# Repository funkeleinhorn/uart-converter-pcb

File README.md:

# My first PCB (an UART Converter)

This is the first PCB I have designed to learn [KiCad](https://www.kicad.org/).
It is an USB-C to UART Converter supporting 3.3V using an [FT230X](https://ftdichip.com/wp-content/uploads/2021/10/DS_FT230X.pdf).
Thanks a lot to [@Cutie-PHY](https://fosstodon.org/@sad_electronics) for teaching me KiCad and helping me to get this PCB designed and manufactured.

This project is licensed as open hardware. See LICENSE.txt for details.

## Images

Here you can see how the PCB looks:

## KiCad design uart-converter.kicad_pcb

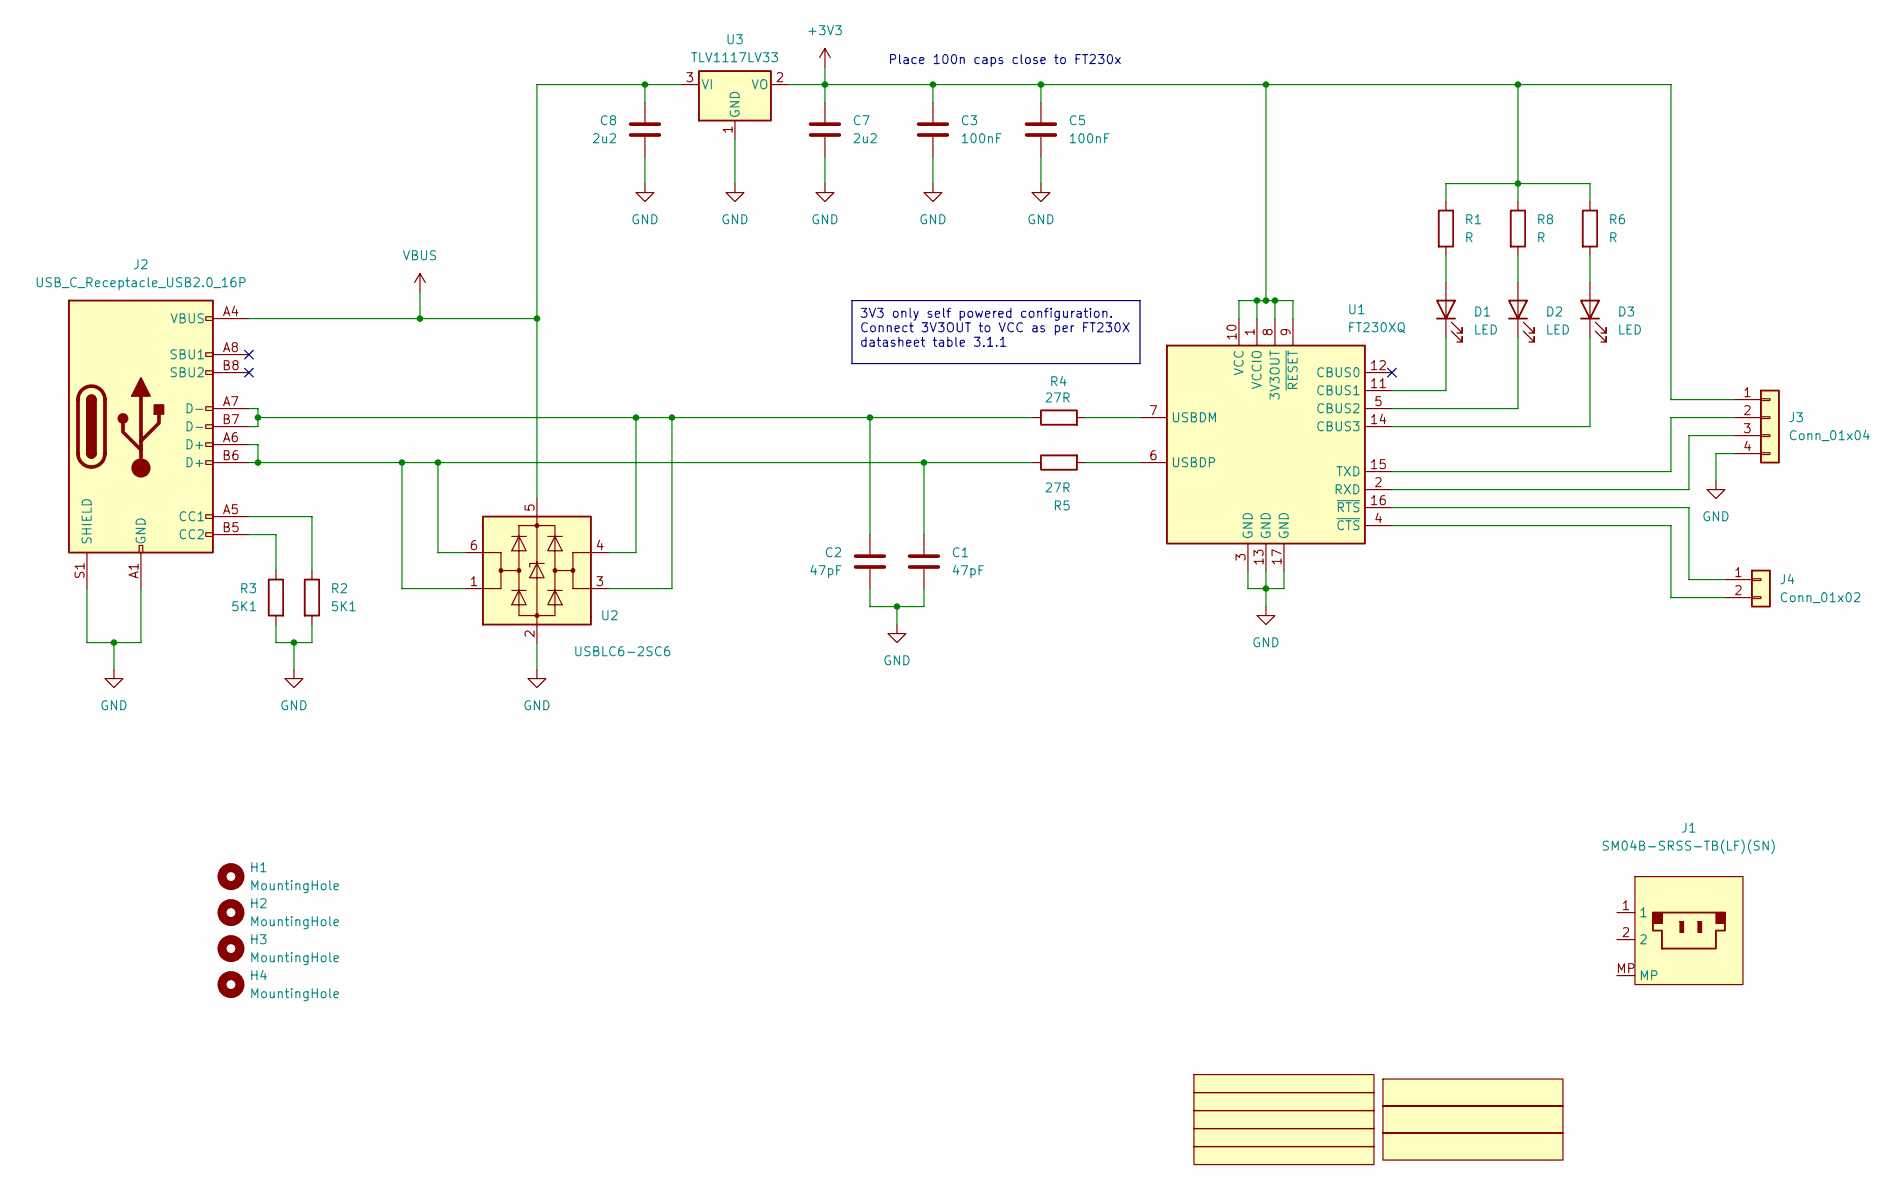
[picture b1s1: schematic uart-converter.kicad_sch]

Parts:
C1, C2: 47pF; C_0603_1608Metric
C3, C5: 100nF; C_0603_1608Metric
C7, C8: 2u2; C_0805_2012Metric
D1, D2, D3: LED; LED_0603_1608Metric
H1, H2, H3, H4: MountingHole; MountingHole_3.2mm_M3_DIN965
J1: SM04B-SRSS-TB(LF)(SN); MPN SM04B-SRSS-TB(LF)(SN)
J2: USB_C_Receptacle_USB2.0_16P; USB_C_Receptacle_JAE_DX07S016JA1R1500
J3: Conn_01x04; PinHeader_1x04_P2.54mm_Horizontal
J4: Conn_01x02; PinHeader_1x02_P2.54mm_Horizontal
R1, R6, R8: R; R_0603_1608Metric
R2, R3: 5K1; R_0603_1608Metric
R4, R5: 27R; R_0603_1608Metric
U1: FT230XQ; QFN-16-1EP_4x4mm_P0.65mm_EP2.1x2.1mm
U2: USBLC6-2SC6; SOT-23-6
U3: TLV1117LV33; SOT-223-3_TabPin2

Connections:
+3V3: C3.1, C5.1, C7.1, J3.1, R1.1, R6.1, R8.1, U1.1 (VCCIO), U1.8 (3V3OUT), U1.9 (~RESET), U1.10 (VCC), U3.2 (VO)
GND: C1.2, C2.2, C3.2, C5.2, C7.2, C8.2, J2.A1 (GND), J2.A12 (GND), J2.B1 (GND), J2.B12 (GND), J2.S1 (SHIELD), J3.4, R2.2, R3.2, U1.3 (GND), U1.13 (GND), U1.17 (GND), U2.2 (GND), U3.1 (GND)
unnamed: C1.1, J2.A6 (D+), J2.B6 (D+), R5.1, U2.1 (I/O1), U2.6 (I/O1)
unnamed: C2.1, J2.A7 (D-), J2.B7 (D-), R4.1, U2.3 (I/O2), U2.4 (I/O2)
unnamed: D1.2 (A), R1.2
unnamed: D1.1 (K), U1.11 (CBUS1)
unnamed: D2.2 (A), R8.2
unnamed: D2.1 (K), U1.5 (CBUS2)
unnamed: D3.2 (A), R6.2
unnamed: D3.1 (K), U1.14 (CBUS3)
unnamed: J2.A5 (CC1), R2.1
unnamed: J2.B5 (CC2), R3.1
unnamed: J3.2, U1.15 (TXD)
unnamed: J3.3, U1.2 (RXD)
unnamed: J4.1, U1.16 (~RTS)
unnamed: J4.2, U1.4 (~CTS)
unnamed: R4.2, U1.7 (USBDM)
unnamed: R5.2, U1.6 (USBDP)
VBUS: C8.1, J2.A4 (VBUS), J2.A9 (VBUS), J2.B4 (VBUS), J2.B9 (VBUS), U2.5 (VBUS), U3.3 (VI)

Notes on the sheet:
3V3 only self powered configuration. Connect 3V3OUT to VCC as per FT230X datasheet table 3.1.1
Place 100n caps close to FT230x

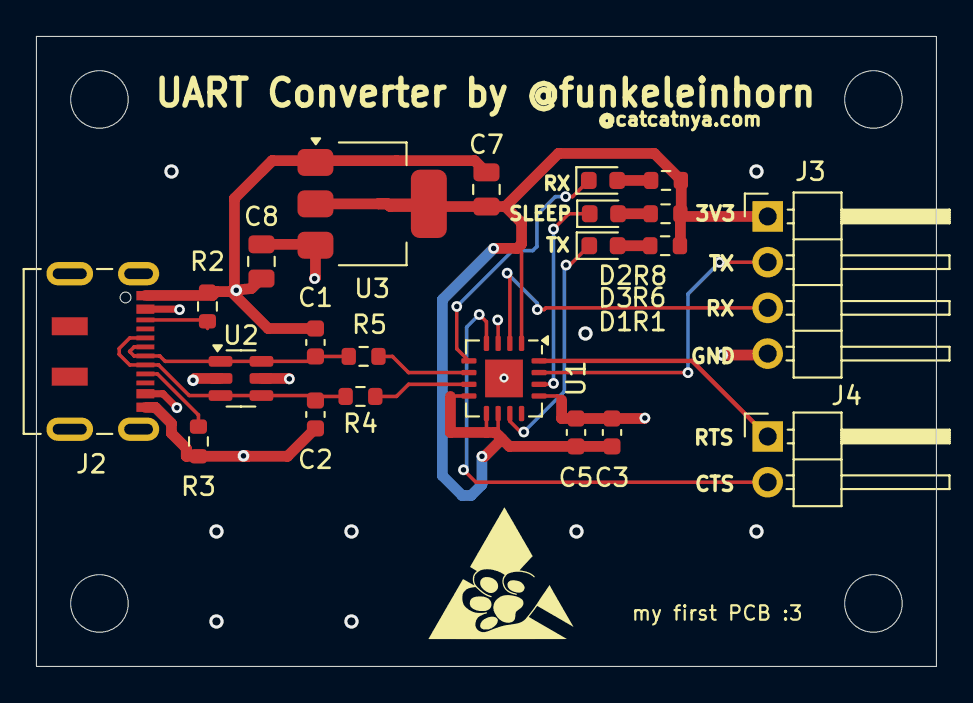
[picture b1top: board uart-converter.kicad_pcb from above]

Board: 4 copper layers, 50.0 x 35.0 mm, 26 parts (0 on the bottom side), 19 nets.

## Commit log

2024-05-09 Initial 4-layer version of my PCB.
    This is the first version of my UART-converter.
    I have manufactured 9 units of this to give away some at GPN22.
